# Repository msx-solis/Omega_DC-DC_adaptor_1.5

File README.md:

# Omega_DC-DC_adaptor
Actualización de la entrada de corriente para el OMEGA HOME COMPUTER

## v. 1.6
Mejorada la distribución de fusibles para independizar el fusible de cada canal 5v, anteriormente el fusible de la placa base y la unidad de discos era común, ahora hay un fusible independiente para ambas vias.

También se ha añadido una doble hilera de pines (J7 y J10) para permitir la conexión a la placa base con más de un tipo de conector (uno que conecta recto y otro que desplaza la conexión 2.54mm).

## v. 1.5
Este circuito mejora la seguridad y comodidad para la interconexión del circuito mini fuente DC-DC +12v -12v a la placa base del OMEGA HOME COMPUTER.
Permite la conexión de un interruptor de apagado, con una resistencia de descarga rapida, y también utilizar varios fusibles, uno por cada línea de tensión independiente.

Además incorpora varios enchufes independientes de alimnetación para conectar diversas ampliaciones internas en la carcasa, cada una unida a una conexión de fusible asociada.

La función que tienen el 1N4007 y el diodo zener es de protección, evitando daños en caso de una alimentación de polaridad inversa o de un voltaje algo superior.

Los valores de los fusibles rearmables son una sugerencia obtenida de las mediciones en mi equipo y con mis accesorios.

Hay varias versiones anteriores que no tenían fusibles ni conexión para interruptor.

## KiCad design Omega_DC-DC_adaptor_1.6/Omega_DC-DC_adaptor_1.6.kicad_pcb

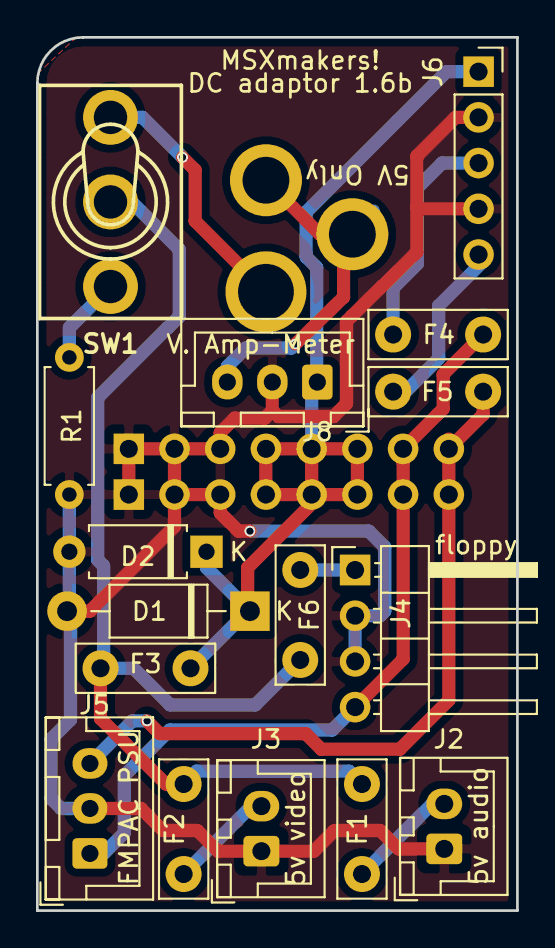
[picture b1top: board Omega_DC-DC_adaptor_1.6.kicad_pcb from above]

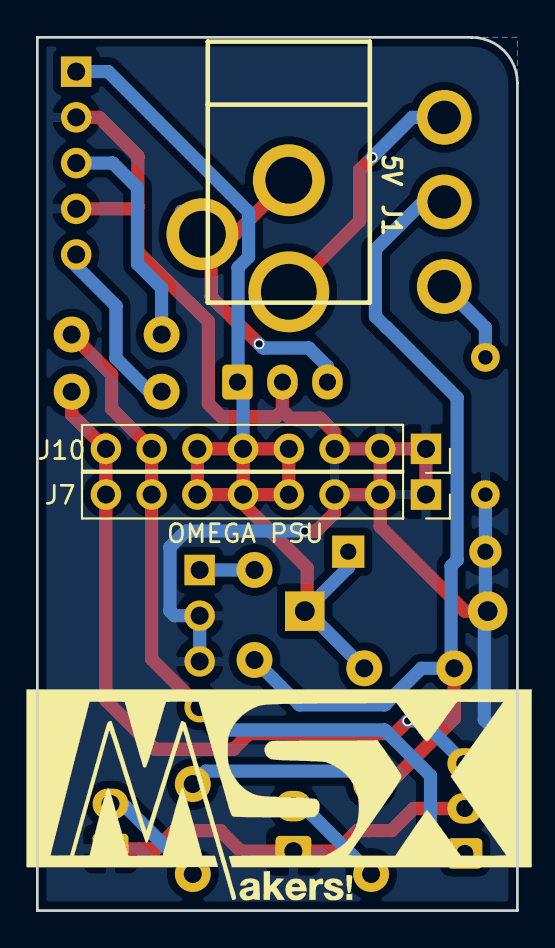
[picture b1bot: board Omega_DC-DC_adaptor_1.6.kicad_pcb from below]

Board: 2 copper layers, 26.7 x 48.5 mm, 19 parts (3 on the bottom side), 13 nets.

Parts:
D1: 1N4007; D_DO-41_SOD81_P10.16mm_Horizontal
D2: 5.6V; D_A-405_P7.62mm_Horizontal
F1, F2, F3, F6: 1,5A; C_Disc_D7.5mm_W2.5mm_P5.00mm
F4, F5: 100mA; C_Disc_D7.5mm_W2.5mm_P5.00mm
J1: 5V; Conn_Power_Jack_Circular_Pads
J2: 5v audio; JST_XH_B2B-XH-A_1x02_P2.50mm_Vertical
J3: 5v video; JST_XH_B2B-XH-A_1x02_P2.50mm_Vertical
J4: floppy; PinHeader_1x04_P2.54mm_Horizontal
J5: FMPAC PSU; JST_XH_B3B-XH-A_1x03_P2.50mm_Vertical
J6: POWER; PinSocket_1x05_P2.54mm_Vertical
J7: OMEGA POWER SUPPLY; PinSocket_1x08_P2.54mm_Vertical
J8: V. Amp-Meter; JST_XH_B3B-XH-A_1x03_P2.50mm_Vertical
J10: OMEGA PSU; PinSocket_1x08_P2.54mm_Vertical
R1: 150; R_Axial_DIN0207_L6.3mm_D2.5mm_P7.62mm_Horizontal
SW1: POWER SWITCH; SWITCH_SPDT

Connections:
GND: D1.2, D2.2, J2.1, J3.1, J4.2, J4.3, J5.2, J6.2, J6.4, J7.1, J7.2, J7.3, J8.2, J10.1, J10.2, J10.3, R1.2
unnamed: F1.1, J2.2
unnamed: F1.2, F2.2, F3.2, F6.2, SW1.2
unnamed: F2.1, J3.2
unnamed: F4.2, J6.3
unnamed: F5.2, J6.5
unnamed: F6.1, J4.1
unnamed: J1.1, SW1.1
unnamed: J1.2, J1.3, J8.3
unnamed: R1.1, SW1.3
VCC: D1.1, D2.1, F3.1, J6.1, J7.4, J7.5, J7.6, J8.1, J10.4, J10.5, J10.6
VDD: F4.1, J4.4, J5.1, J7.7, J10.7
VSS: F5.1, J5.3, J7.8, J10.8

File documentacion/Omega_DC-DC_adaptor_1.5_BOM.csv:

Reference,qty,Value,link
D1,1,1N4007,https://es.aliexpress.com/item/1005001456610390.html?spm=a2g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
D2,1,5.6V Zener,https://es.rs-online.com/web/p/products/5443604/
F1,1,Fuse resettable 500mA (trigger 1A),https://es.rs-online.com/web/p/products/5176635/
F2,1,"Fuse resettable 750mA (trigger 1,5A)",https://es.rs-online.com/web/p/products/5176663/
F3,1,"Fuse resettable 1,6A (trigger 3,2A)",https://es.rs-online.com/web/p/products/5176792/
"F4, F5",2,Fuse resettable 50mA (trigger 100mA),https://es.rs-online.com/web/p/products/6478421/
J1,1,"DC Power Jack, 2,1mm",https://es.aliexpress.com/item/33005175186.html?spm=a2g0s.90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
J10,1,1x08 female pinheader,https://es.aliexpress.com/item/33011682095.html?spm=a2g0s.90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
"J2, J3",2,2 pin male PCB JST vertical connector,"https://es.aliexpress.com/item/32855763468.html?spm=a2g0o.de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,scm-url:1007.14452.226710.0,pvid:8dca3c1c-82d4-4767-aaa4-716c7a224aaf,tpp_buckets:668%230%23131923%2367_668%23888%233325%2315_4452%230%23226710%230_4452%233474%2316498%23728_4452%234862%2324463%23547_4452%233098%239599%23680_4452%235108%2323442%23388_4452%233564%2316062%23632_668%232846%238109%231935_668%235811%2327178%2332_668%236421%2330829%23783_668%232717%237564%23674_668%231000022185%231000066058%230_668%236808%2332778%23995_668%233422%2315392%23315_23416%230%23213724%230_23416%236336%2330490%236_23416%234721%2321967%23754_23416%234722%2321972%237&&pdp_ext_f=%7B%22sceneId%22:%2223416%22%7D&fromDetail"
J4,1,"4 pin male connector. 2,54mm 90 degrees",https://es.aliexpress.com/item/33053313994.html?spm=a2g0o.pr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
J5,1,3 pin male PCB JST vertical connector,"https://es.aliexpress.com/item/32855763468.html?spm=a2g0o.de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,scm-url:1007.14452.226710.0,pvid:8dca3c1c-82d4-4767-aaa4-716c7a224aaf,tpp_buckets:668%230%23131923%2367_668%23888%233325%2315_4452%230%23226710%230_4452%233474%2316498%23728_4452%234862%2324463%23547_4452%233098%239599%23680_4452%235108%2323442%23388_4452%233564%2316062%23632_668%232846%238109%231935_668%235811%2327178%2332_668%236421%2330829%23783_668%232717%237564%23674_668%231000022185%231000066058%230_668%236808%2332778%23995_668%233422%2315392%23315_23416%230%23213724%230_23416%236336%2330490%236_23416%234721%2321967%23754_23416%234722%2321972%237&&pdp_ext_f=%7B%22sceneId%22:%2223416%22%7D&fromDetail"
J6,1,1x05 female straight pinheader,https://es.aliexpress.com/item/4000557204854.html?spm=a2g0o.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
no REF,1,SPDT ON-ON 6A switch,https://es.aliexpress.com/item/1005001667810183.html?spm=a2g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
PCB,1,mini DC-DC 1.5 PCB adaptor with fuses,https://msxmakers.design.blog/2021/07/16/personaliza-tu-omeg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
R1,1,120 ohm 250mW,"https://es.aliexpress.com/item/32952657927.html?spm=a2g0o.pr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,searchwe"
SW1,1,3 way male terminal block,https://es.rs-online.com/web/p/products/8970730/

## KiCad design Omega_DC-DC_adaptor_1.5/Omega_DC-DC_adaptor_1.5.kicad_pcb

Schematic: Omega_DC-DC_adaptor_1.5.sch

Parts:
D1: 1N4007; D_DO-41_SOD81_P10.16mm_Horizontal
D2: 5.6V; D_A-405_P7.62mm_Horizontal
F1, F2, F3: 1,5A; C_Disc_D7.5mm_W2.5mm_P5.00mm
F4, F5: 100mA; C_Disc_D7.5mm_W2.5mm_P5.00mm
J1: 5V; Conn_Power_Jack_Circular_Pads
J2: 5v audio; JST_XH_B2B-XH-AM_1x02_P2.50mm_Vertical
J3: 5v video; JST_XH_B2B-XH-AM_1x02_P2.50mm_Vertical
J4: floppy; PinHeader_1x04_P2.54mm_Horizontal
J5: FMPAC; JST_XH_B3B-XH-AM_1x03_P2.50mm_Vertical
J6: POWER; PinSocket_1x05_P2.54mm_Vertical
J10: POWER; PinSocket_1x08_P2.54mm_Vertical
R1: 100; R_Axial_DIN0207_L6.3mm_D2.5mm_P7.62mm_Horizontal
SW1: SW_SPDT; SWITCH_SPDT

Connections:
GND: D1.2, D2.2, J1.2, J1.3, J2.1, J3.1, J4.2, J4.3, J5.2, J6.2, J6.4, J10.1, J10.2, J10.3, R1.2
unnamed: F1.1, J2.2
unnamed: F1.2, F2.2, F3.2, SW1.2
unnamed: F2.1, J3.2
unnamed: F4.2, J6.3
unnamed: F5.2, J6.5
unnamed: J1.1, SW1.3
unnamed: R1.1, SW1.1
VCC: D1.1, D2.1, F3.1, J4.1, J6.1, J10.4, J10.5, J10.6
VDD: F4.1, J4.4, J5.1, J10.7
VSS: F5.1, J5.3, J10.8

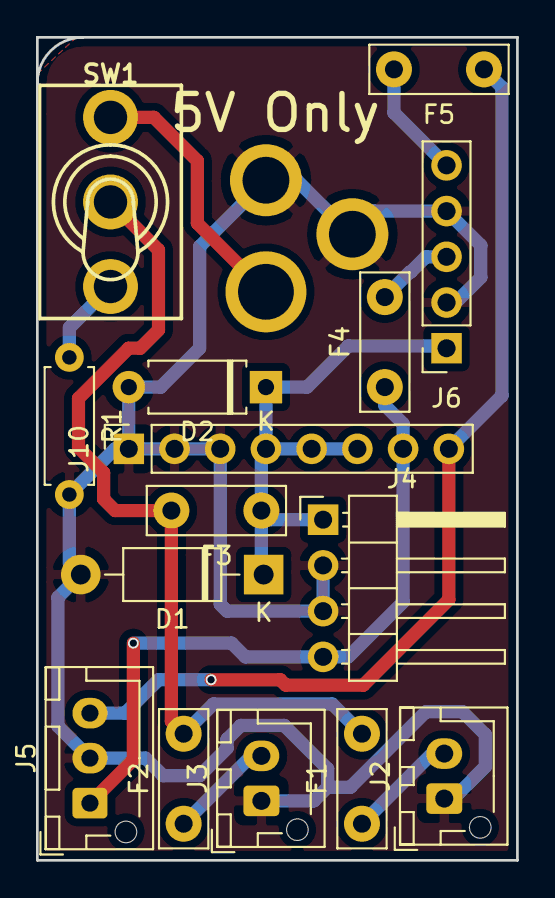
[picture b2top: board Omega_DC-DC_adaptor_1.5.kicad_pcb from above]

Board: 2 copper layers, 26.7 x 45.7 mm, 16 parts (1 on the bottom side), 11 nets.

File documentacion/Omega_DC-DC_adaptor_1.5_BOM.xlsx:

Reference | qty | Value | link
D1 | 1 | 1N4007 | https://es.aliexpress.com/item/1005001456610390.html?spm=a2g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
D2 | 1 | 5.6V Zener | https://es.rs-online.com/web/p/products/5443604/
F1 | 1 | Fuse resettable 500mA (trigger 1A) | https://es.rs-online.com/web/p/products/5176635/
F2 | 1 | Fuse resettable 750mA (trigger 1,5A) | https://es.rs-online.com/web/p/products/5176663/
F3 | 1 | Fuse resettable 1,6A (trigger 3,2A) | https://es.rs-online.com/web/p/products/5176792/
F4, F5 | 2 | Fuse resettable 50mA (trigger 100mA) | https://es.rs-online.com/web/p/products/6478421/
J1 | 1 | DC Power Jack, 2,1mm | https://es.aliexpress.com/item/33005175186.html?spm=a2g0s.90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
J10 | 1 | 1x08 female pinheader | https://es.aliexpress.com/item/33011682095.html?spm=a2g0s.90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
J2, J3 | 2 | 2 pin male PCB JST vertical connector | https://es.aliexpress.com/item/32855763468.html?spm=a2g0o.de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
J4 | 1 | 4 pin male connector. 2,54mm 90 degrees | https://es.aliexpress.com/item/33053313994.html?spm=a2g0o.pr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
J5 | 1 | 3 pin male PCB JST vertical connector | https://es.aliexpress.com/item/32855763468.html?spm=a2g0o.de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
J6 | 1 | 1x05 female straight pinheader | https://es.aliexpress.com/item/4000557204854.html?spm=a2g0o.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
no REF | 1 | SPDT ON-ON 6A switch | https://es.aliexpress.com/item/1005001667810183.html?spm=a2g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
PCB | 1 | mini DC-DC 1.5 PCB adaptor with fuses | https://msxmakers.design.blog/2021/07/16/personaliza-tu-omeg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
R1 | 1 | 120 ohm 250mW | https://es.aliexpress.com/item/32952657927.html?spm=a2g0o.pr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
SW1 | 1 | 3 way male terminal block | https://es.rs-online.com/web/p/products/8970730/
